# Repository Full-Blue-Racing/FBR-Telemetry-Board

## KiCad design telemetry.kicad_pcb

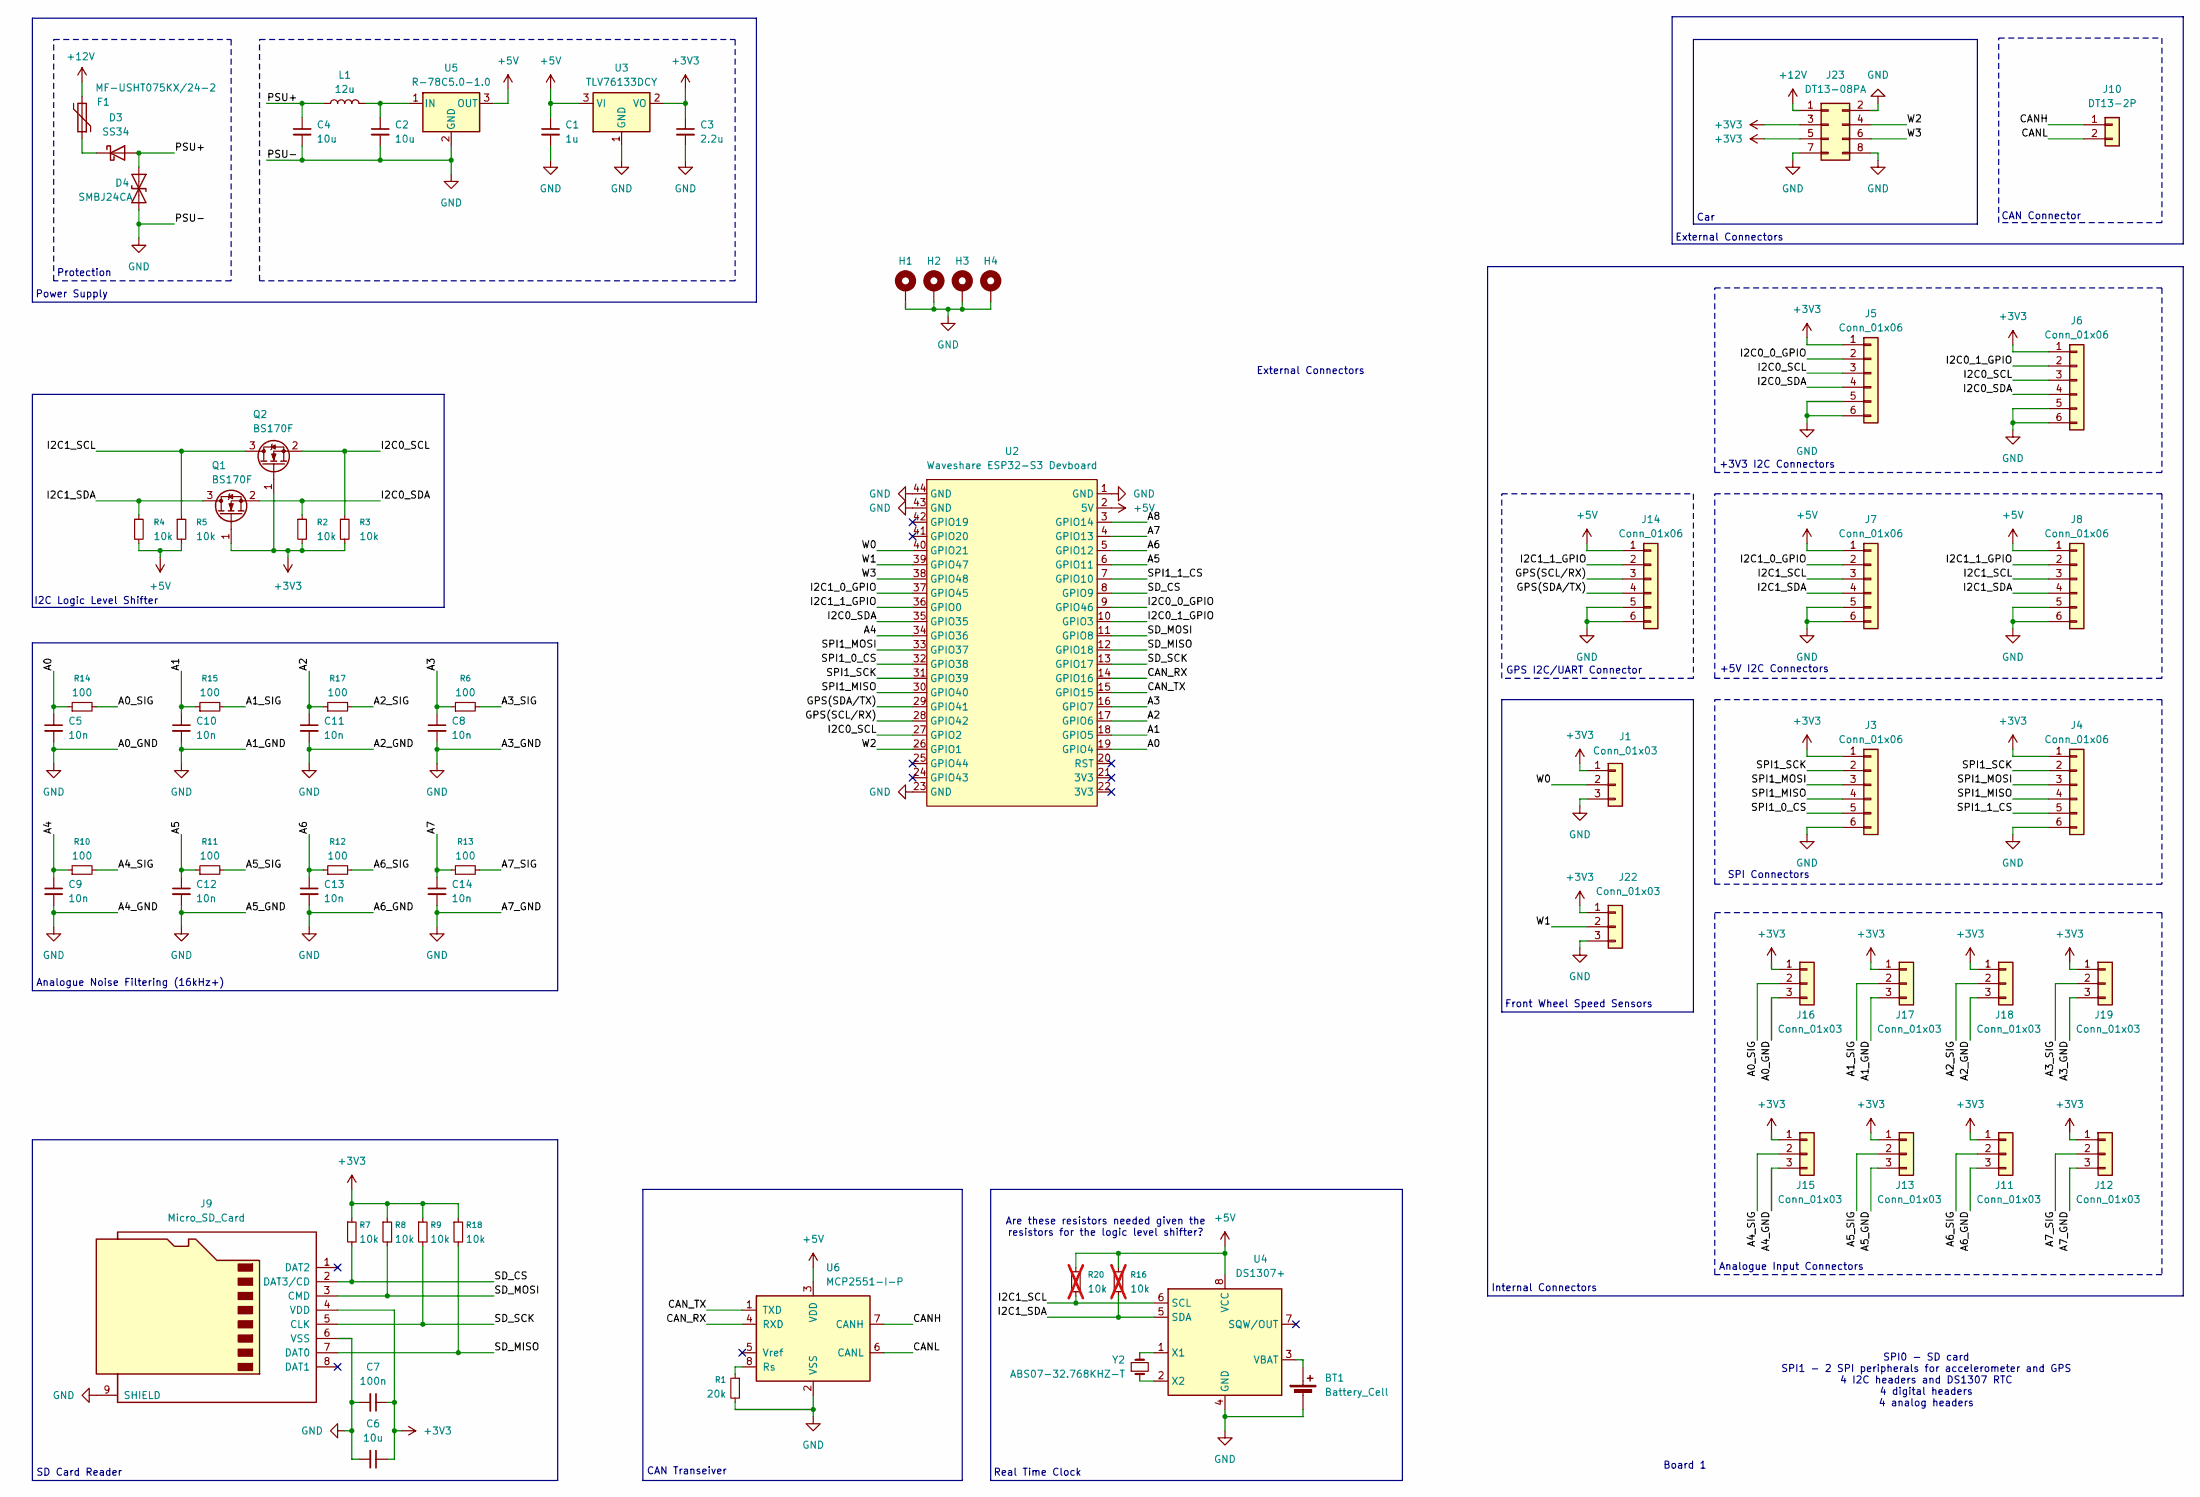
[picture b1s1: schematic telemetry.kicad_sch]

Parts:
BT1: Battery_Cell; RSPRO_237-8341
C1: 1u; C_0805_2012Metric
C2, C4, C6: 10u; C_0805_2012Metric
C3: 2.2u; C_0805_2012Metric
C5, C8, C9, C10, C11, C12, C13, C14: 10n; C_0805_2012Metric
C7: 100n; C_0805_2012Metric
D3: SS34; D_SMA
D4: SMBJ24CA; D_SMB
F1: MF-USHT075KX/24-2; L_1210_3225Metric
H1, H2, H3, H4: MountingHole_Pad; MountingHole_3.2mm_M3_DIN965_Pad
J1, J11, J12, J13, J15, J16, J17, J18, J19, J22: Conn_01x03; JST_XA_B03B-XASK-1_1x03_P2.50mm_Vertical
J3, J4, J5, J6, J7, J8, J14: Conn_01x06; JST_XA_B06B-XASK-1_1x06_P2.50mm_Vertical
J9: Micro_SD_Card; microSD_HC_Hirose_DM3AT-SF-PEJM5
J10: DT13-2P; TE_DT13-2P
J23: DT13-08PA; TE_DT13-08PA
L1: 12u; L_6.3x6.3_H3
Q1, Q2: BS170F; SOT-23
R1: 20k; R_0805_2012Metric
R2, R3, R4, R5, R7, R8, R9, R18: 10k; R_0805_2012Metric
R6, R10, R11, R12, R13, R14, R15, R17: 100; R_0805_2012Metric
R16, R20: 10k; R_0805_2012Metric; not fitted
U2: Waveshare ESP32-S3 Devboard
U3: TLV76133DCY; SOT-223-3_TabPin2
U4: DS1307+; DIP-8_W7.62mm
U5: R-78C5.0-1.0; Converter_DCDC_RECOM_R-78E-0.5_THT
U6: MCP2551-I-P; DIP-8_W7.62mm
Y2: ABS07-32.768KHZ-T; XTAL_ABS07-32.768KHZ-T

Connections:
+3V3: C3.1, C6.1, C7.1, J1.1, J3.1, J4.1, J5.1, J6.1, J9.4 (VDD), J11.1, J12.1, J13.1, J15.1, J16.1, J17.1, J18.1, J19.1, J22.1, J23.3, J23.5, Q1.1 (G), Q2.1 (G), R2.2, R3.2, R7.1, R8.1, R9.1, R18.1, U3.2 (VO)
+5V: C1.1, J7.1, J8.1, J14.1, R4.2, R5.2, R16.1, R20.1, U2.2 (5V), U3.3 (VI), U4.8 (VCC), U5.3 (OUT), U6.3 (VDD)
+12V: F1.2, J23.1
/A0: C5.1, R14.1, U2.19 (GPIO4)
/A0_SIG: J16.2, R14.2
/A1: C10.1, R15.1, U2.18 (GPIO5)
/A1_SIG: J17.2, R15.2
/A2: C11.1, R17.1, U2.17 (GPIO6)
/A2_SIG: J18.2, R17.2
/A3: C8.1, R6.1, U2.16 (GPIO7)
/A3_SIG: J19.2, R6.2
/A4: C9.1, R10.1, U2.34 (GPIO36)
/A4_SIG: J15.2, R10.2
/A5: C12.1, R11.1, U2.6 (GPIO11)
/A5_SIG: J13.2, R11.2
/A6: C13.1, R12.1, U2.5 (GPIO12)
/A6_SIG: J11.2, R12.2
/A7: C14.1, R13.1, U2.4 (GPIO13)
/A7_SIG: J12.2, R13.2
/A8: U2.3 (GPIO14)
/CANH: J10.1, U6.7 (CANH)
/CANL: J10.2, U6.6 (CANL)
/CAN_RX: U2.14 (GPIO16), U6.4 (RXD)
/CAN_TX: U2.15 (GPIO15), U6.1 (TXD)
/GPS(SCL/RX): J14.3, U2.28 (GPIO42)
/GPS(SDA/TX): J14.4, U2.29 (GPIO41)
/I2C0_0_GPIO: J5.2, U2.9 (GPIO46)
/I2C0_1_GPIO: J6.2, U2.10 (GPIO3)
/I2C0_SCL: J5.3, J6.3, Q2.2 (S), R3.1, U2.27 (GPIO2)
/I2C0_SDA: J5.4, J6.4, Q1.2 (S), R2.1, U2.35 (GPIO35)
/I2C1_0_GPIO: J7.2, U2.37 (GPIO45)
/I2C1_1_GPIO: J8.2, J14.2, U2.36 (GPIO0)
/I2C1_SCL: J7.3, J8.3, Q2.3 (D), R5.1, R20.2, U4.6 (SCL)
/I2C1_SDA: J7.4, J8.4, Q1.3 (D), R4.1, R16.2, U4.5 (SDA)
/PSU+: C4.1, D3.2 (A), D4.1 (A1), L1.1
/SD_CS: J9.2 (DAT3/CD), R7.2, U2.8 (GPIO9)
/SD_MISO: J9.7 (DAT0), R18.2, U2.12 (GPIO18)
/SD_MOSI: J9.3 (CMD), R8.2, U2.11 (GPIO8)
/SD_SCK: J9.5 (CLK), R9.2, U2.13 (GPIO17)
/SPI1_0_CS: J3.5, U2.32 (GPIO38)
/SPI1_1_CS: J4.5, U2.7 (GPIO10)
/SPI1_MISO: J3.4, J4.4, U2.30 (GPIO40)
/SPI1_MOSI: J3.3, J4.3, U2.33 (GPIO37)
/SPI1_SCK: J3.2, J4.2, U2.31 (GPIO39)
/W0: J1.2, U2.40 (GPIO21)
/W1: J22.2, U2.39 (GPIO47)
/W2: J23.4, U2.26 (GPIO1)
/W3: J23.6, U2.38 (GPIO48)
GND: BT1.2 (-), C1.2, C2.2, C3.2, C4.2, C5.2, C6.2, C7.2, C8.2, C9.2, C10.2, C11.2, C12.2, C13.2, C14.2, D4.2 (A2), H1.1, H2.1, H3.1, H4.1, J1.3, J3.6, J4.6, J5.5, J5.6, J6.5, J6.6, J7.5, J7.6, J8.5, J8.6, J9.6 (VSS), J9.9 (SHIELD), J11.3, J12.3, J13.3, J14.5, J14.6, J15.3, J16.3, J17.3, J18.3, J19.3, J22.3, J23.2, J23.7, J23.8, R1.2, U2.1 (GND), U2.23 (GND), U2.43 (GND), U2.44 (GND), U3.1 (GND), U4.4 (GND), U5.2 (GND), U6.2 (VSS)
unnamed: BT1.1 (+), U4.3 (VBAT)
unnamed: D3.1 (K), F1.1
unnamed: U4.1 (X1), Y2.2
unnamed: U4.2 (X2), Y2.1
unnamed: C2.1, L1.2, U5.1 (IN)
unnamed: R1.1, U6.8 (Rs)

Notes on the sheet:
Board 1
External Connectors
Power Supply
CAN Transeiver
SPI Connectors
+3V3 I2C Connectors
Analogue Noise Filtering (16kHz+)
Protection
Car
GPS I2C/UART Connector
I2C Logic Level Shifter
Analogue Input Connectors
SPI0 - SD card SPI1 - 2 SPI peripherals for accelerometer and GPS 4 I2C headers and DS1307 RTC 4 digital headers 4 analog headers
Real Time Clock
SD Card Reader
CAN Connector
Are these resistors needed given the resistors for the logic level shifter?
+5V I2C Connectors
Internal Connectors
Front Wheel Speed Sensors

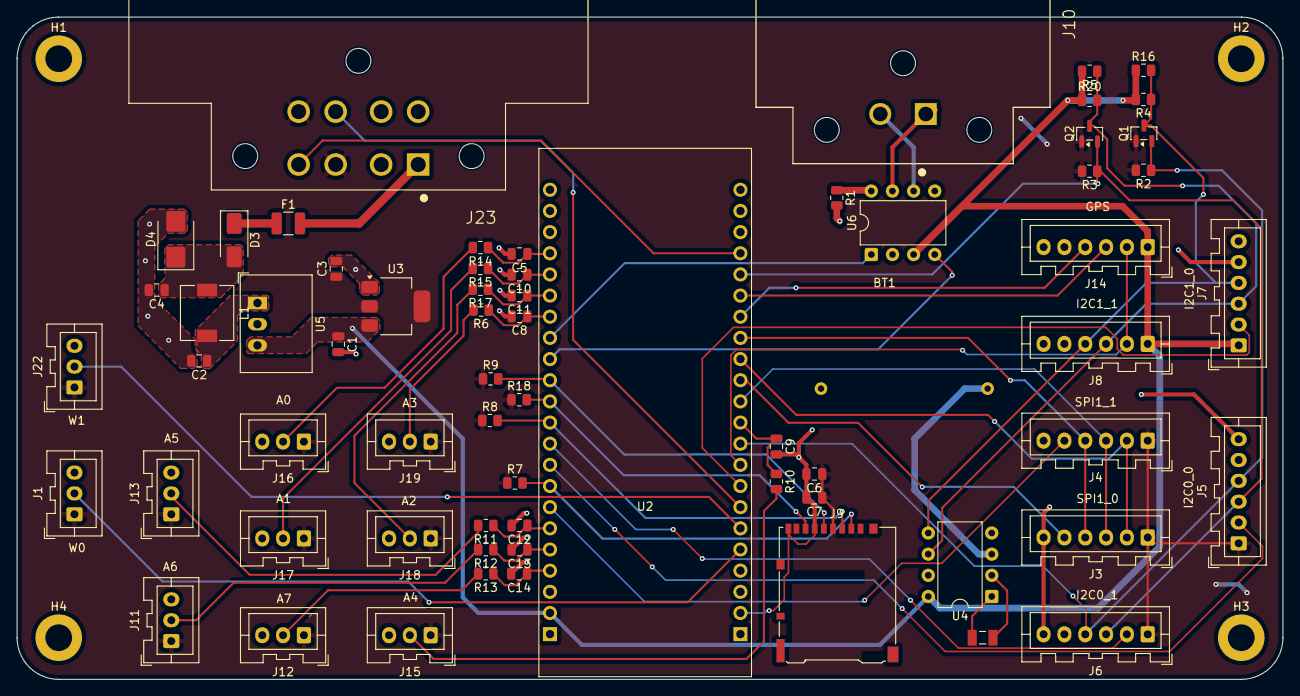
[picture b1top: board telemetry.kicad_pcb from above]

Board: 2 copper layers, 152.0 x 79.5 mm, 71 parts (1 on the bottom side), 54 nets.

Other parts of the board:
Telemetry (2026): LOGO; FBR_Logo_.9in

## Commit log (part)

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2026-03-28 Start git project
2026-03-28 Complete (hopefully) schematic
2026-04-01 added ESP32, connector footprint
2026-04-13 Place and route important components
2026-04-13 Add +3V3 pin to internal WSS connectors
2026-04-13 Switch to SIG+3V3 for Back WSS
2026-04-15 Arranged remaining components, added few tracks
2026-04-15 Slim board
2026-04-16 did some traces
2026-04-16 moved traces from psu
2026-04-16 Move ESP32 to center
2026-04-17 Fix DRC errors
2026-04-17 Add text and labels
